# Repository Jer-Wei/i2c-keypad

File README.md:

i2c-keyboard.
=============

I've been running in to the problem a few times where I wanted to use an array style [keypad](https://tronixlabs.com.au/components/buttons/keypads/sealed-membrane-keypad-4x4-button-pad-with-sticker-australia/).

So here's my solution, an attiny 84 based i2c solution

CREDITS
------------

This project was designed by [John Spencer](https://github.com/mage0r)

Made at hackmelbourne.org!

SPECIAL THANKS
------------

To the HackMelbourne (CCHS, http://hackmelbourne.org) community of Melbourne, Australia.

To all other open-source developers whose countless hours supported every other aspect of this design.

DISTRIBUTION
------------
The specific terms of distribution of this project are governed by the
license referenced below. Please contact the copyright owner if you wish to modify the board for distribution. Please utilize this design for personal or research projects. Please acknowledge all contributors.

LICENSE
-------
Licensed under the TAPR Open Hardware License (www.tapr.org/OHL).
A plain text version of this license is included in this directory.

Copyright John Spencer 2016

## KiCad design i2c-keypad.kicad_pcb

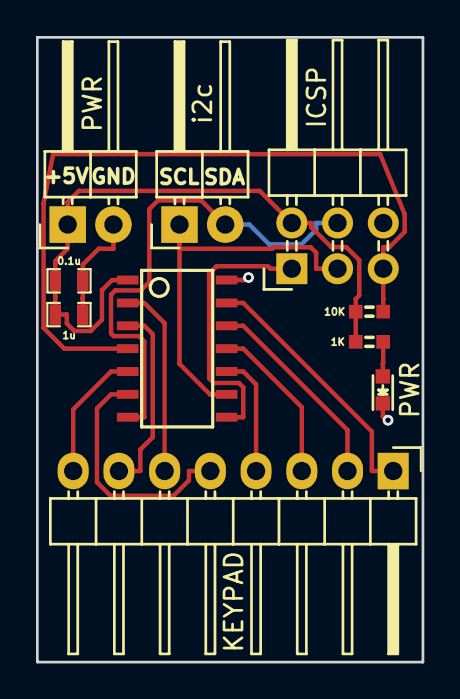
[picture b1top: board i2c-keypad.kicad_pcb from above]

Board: 2 copper layers, 21.4 x 34.7 mm, 10 parts (0 on the bottom side), 15 nets.

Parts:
C1: 0.1u; 0603_CAP
C2: 1u; 0603_CAP
D1: PWR; LED_0603
IC1: ATTINY84-S; SO14_4mm
P1: ICSP; Pin_Header_Angled_2x03
P2: i2c; Pin_Header_Angled_1x02
P3: PWR; Pin_Header_Angled_1x02
P4: KEYPAD; Pin_Header_Angled_1x08
R1: 10K; 0603
R2: 1K; 0603

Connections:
+5V: C1.1, C2.1, IC1.1, P1.2, P3.1, R1.1, R2.1
/MISO: IC1.8, P1.1
/MOSI: IC1.7, P1.4, P2.2
/RST: IC1.4, P1.5, R1.2
/SCK: IC1.9, P1.3, P2.1
GND: C1.2, C2.2, D1.1, IC1.14, P1.6, P3.2
unnamed: D1.2, R2.2
unnamed: IC1.2, P4.6
unnamed: IC1.3, P4.7
unnamed: IC1.5, P4.8
unnamed: IC1.6, P4.5
unnamed: IC1.10, P4.4
unnamed: IC1.11, P4.3
unnamed: IC1.12, P4.2
unnamed: IC1.13, P4.1

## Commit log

2016-08-14 :neckbeard: Added .gitattributes
2016-08-14 Initial Check in
2016-08-14 Added Image
2016-12-20 Yep, ground plane. caught again.
